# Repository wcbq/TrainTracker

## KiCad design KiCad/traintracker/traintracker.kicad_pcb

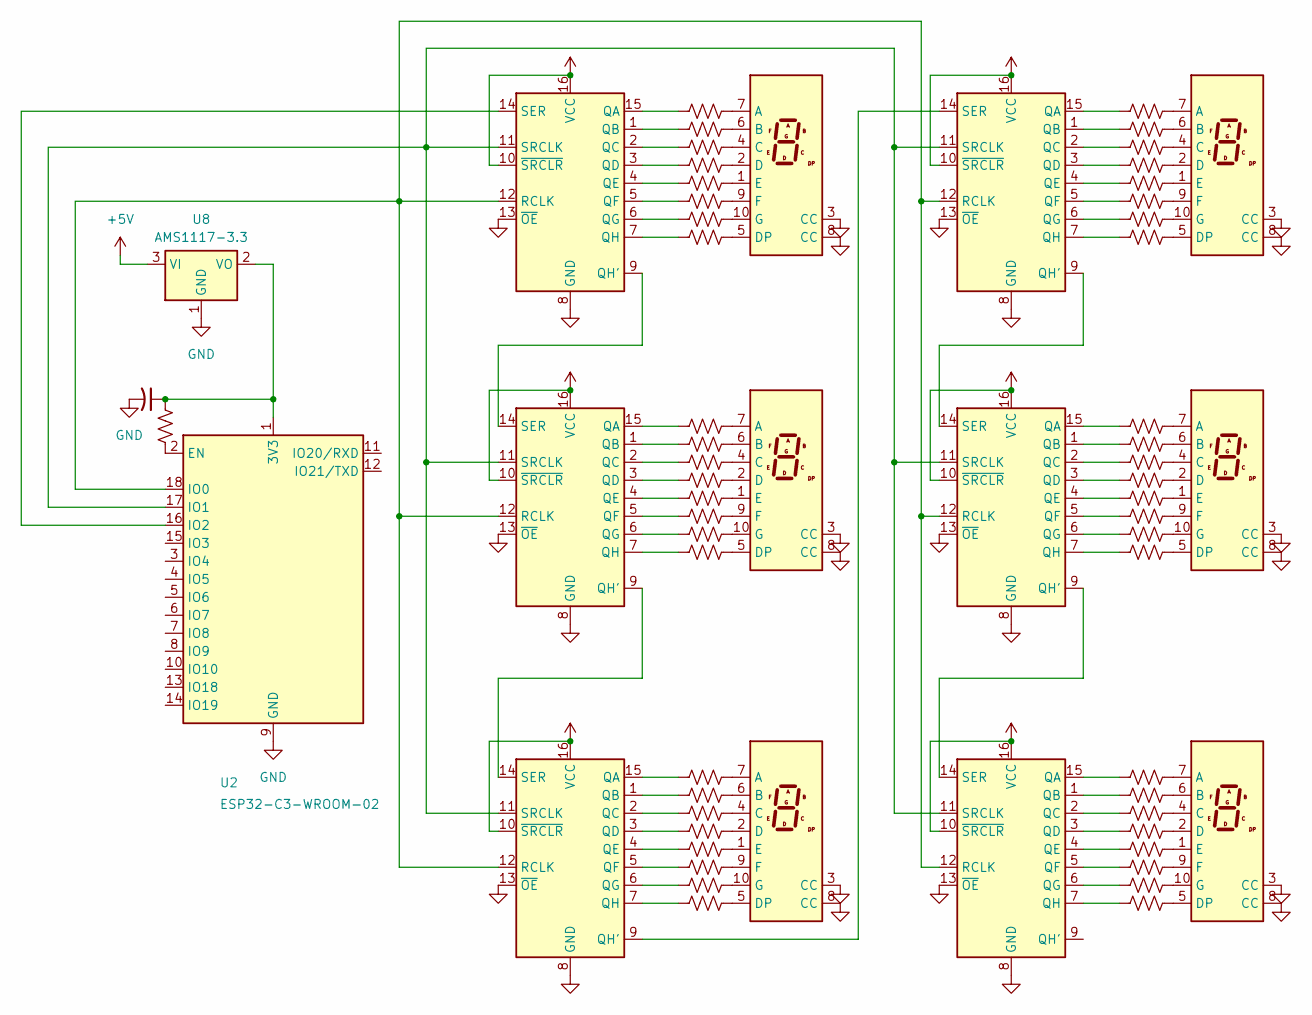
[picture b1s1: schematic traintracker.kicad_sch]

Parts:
C2: C_Small_US; CP_Elec_3x5.3
R1, R2, R3, R4, R5, R6, R7, R8, R9, R10, R11, R12, R13, R14, R15, R16, R17, R18, R19, R20, R21, R22, R23, R24, R25, R26, R27, R28, R29, R30, R31, R32, R33, R34, R35, R36, R37, R38, R39, R40, R41, R42, R43, R44, R45, R46, R47, R48, R50: R_US; R_0201_0603Metric
U1, U3, U4, U5, U6, U7: 74HC595; SOIC-16_3.9x9.9mm_P1.27mm
U2: ESP32-C3-WROOM-02
U8: AMS1117-3.3; SOT-223-3_TabPin2
U15, U16, U17, U18, U19, U20: D168K; D1X8K

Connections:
+5V: U1.10 (~SRCLR), U1.16 (VCC), U3.10 (~SRCLR), U3.16 (VCC), U4.10 (~SRCLR), U4.16 (VCC), U5.10 (~SRCLR), U5.16 (VCC), U6.10 (~SRCLR), U6.16 (VCC), U7.10 (~SRCLR), U7.16 (VCC), U8.3 (VI)
GND: C2.2, U1.8 (GND), U1.13 (~OE), U2.9 (GND), U2.19 (GND), U3.8 (GND), U3.13 (~OE), U4.8 (GND), U4.13 (~OE), U5.8 (GND), U5.13 (~OE), U6.8 (GND), U6.13 (~OE), U7.8 (GND), U7.13 (~OE), U8.1 (GND), U15.3 (CC), U15.8 (CC), U16.3 (CC), U16.8 (CC), U17.3 (CC), U17.8 (CC), U18.3 (CC), U18.8 (CC), U19.3 (CC), U19.8 (CC), U20.3 (CC), U20.8 (CC)
unnamed: R1.2, U1.15 (QA)
unnamed: R2.2, U1.1 (QB)
unnamed: R3.2, U1.2 (QC)
unnamed: R4.2, U1.3 (QD)
unnamed: R5.2, U1.4 (QE)
unnamed: R6.2, U1.5 (QF)
unnamed: R7.2, U1.6 (QG)
unnamed: U1.9 (QH'), U3.14 (SER)
unnamed: R8.2, U1.7 (QH)
unnamed: U1.12 (RCLK), U2.18 (IO0), U3.12 (RCLK), U4.12 (RCLK), U5.12 (RCLK), U6.12 (RCLK), U7.12 (RCLK)
unnamed: U1.14 (SER), U2.16 (IO2)
unnamed: U1.11 (SRCLK), U2.17 (IO1), U3.11 (SRCLK), U4.11 (SRCLK), U5.11 (SRCLK), U6.11 (SRCLK), U7.11 (SRCLK)
unnamed: C2.1, R50.1, U2.1 (3V3), U8.2 (VO)
unnamed: R50.2, U2.2 (EN)
unnamed: R9.2, U3.15 (QA)
unnamed: R10.2, U3.1 (QB)
unnamed: R11.2, U3.2 (QC)
unnamed: R12.2, U3.3 (QD)
unnamed: R13.2, U3.4 (QE)
unnamed: R14.2, U3.5 (QF)
unnamed: R15.2, U3.6 (QG)
unnamed: U3.9 (QH'), U4.14 (SER)
unnamed: R16.2, U3.7 (QH)
unnamed: R17.2, U4.15 (QA)
unnamed: R18.2, U4.1 (QB)
unnamed: R19.2, U4.2 (QC)
unnamed: R20.2, U4.3 (QD)
unnamed: R21.2, U4.4 (QE)
unnamed: R22.2, U4.5 (QF)
unnamed: R23.2, U4.6 (QG)
unnamed: U4.9 (QH'), U5.14 (SER)
unnamed: R24.2, U4.7 (QH)
unnamed: R25.2, U5.15 (QA)
unnamed: R26.2, U5.1 (QB)
unnamed: R27.2, U5.2 (QC)
unnamed: R28.2, U5.3 (QD)
unnamed: R29.2, U5.4 (QE)
unnamed: R30.2, U5.5 (QF)
unnamed: R31.2, U5.6 (QG)
unnamed: U5.9 (QH'), U6.14 (SER)
unnamed: R32.2, U5.7 (QH)
unnamed: R33.2, U6.15 (QA)
unnamed: R34.2, U6.1 (QB)
unnamed: R35.2, U6.2 (QC)
unnamed: R36.2, U6.3 (QD)
unnamed: R37.2, U6.4 (QE)
unnamed: R38.2, U6.5 (QF)
unnamed: R39.2, U6.6 (QG)
unnamed: U6.9 (QH'), U7.14 (SER)
unnamed: R40.2, U6.7 (QH)
unnamed: R41.2, U7.15 (QA)
unnamed: R42.2, U7.1 (QB)
unnamed: R43.2, U7.2 (QC)
unnamed: R44.2, U7.3 (QD)
unnamed: R45.2, U7.4 (QE)
unnamed: R46.2, U7.5 (QF)
unnamed: R47.2, U7.6 (QG)
unnamed: R48.2, U7.7 (QH)
unnamed: R1.1, U15.7 (A)
unnamed: R2.1, U15.6 (B)
unnamed: R3.1, U15.4 (C)
unnamed: R4.1, U15.2 (D)
unnamed: R8.1, U15.5 (DP)
unnamed: R5.1, U15.1 (E)
unnamed: R6.1, U15.9 (F)
unnamed: R7.1, U15.10 (G)
unnamed: R9.1, U16.7 (A)
unnamed: R10.1, U16.6 (B)
unnamed: R11.1, U16.4 (C)
unnamed: R12.1, U16.2 (D)
unnamed: R16.1, U16.5 (DP)
unnamed: R13.1, U16.1 (E)
unnamed: R14.1, U16.9 (F)
unnamed: R15.1, U16.10 (G)
unnamed: R25.1, U17.7 (A)
unnamed: R26.1, U17.6 (B)
unnamed: R27.1, U17.4 (C)
unnamed: R28.1, U17.2 (D)
unnamed: R32.1, U17.5 (DP)
unnamed: R29.1, U17.1 (E)
unnamed: R30.1, U17.9 (F)
unnamed: R31.1, U17.10 (G)
unnamed: R17.1, U18.7 (A)
unnamed: R18.1, U18.6 (B)
unnamed: R19.1, U18.4 (C)
unnamed: R20.1, U18.2 (D)
unnamed: R24.1, U18.5 (DP)
unnamed: R21.1, U18.1 (E)
unnamed: R22.1, U18.9 (F)
unnamed: R23.1, U18.10 (G)
unnamed: R33.1, U19.7 (A)
unnamed: R34.1, U19.6 (B)
unnamed: R35.1, U19.4 (C)
unnamed: R36.1, U19.2 (D)
unnamed: R40.1, U19.5 (DP)
unnamed: R37.1, U19.1 (E)
unnamed: R38.1, U19.9 (F)
unnamed: R39.1, U19.10 (G)
unnamed: R41.1, U20.7 (A)
unnamed: R42.1, U20.6 (B)
unnamed: R43.1, U20.4 (C)
unnamed: R44.1, U20.2 (D)
unnamed: R48.1, U20.5 (DP)
unnamed: R45.1, U20.1 (E)
unnamed: R46.1, U20.9 (F)
unnamed: R47.1, U20.10 (G)

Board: 2 copper layers, 64 parts (0 on the bottom side), 108 nets, no tracks yet.

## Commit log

2026-05-04 Add datasheets
    add datasheets for 7 segment display(3191AS) and shift register (SNx4HC595)
2026-05-04 Upload KiCad
    Add current KiCad files
2026-05-04 Add apitest.py
    test file for getting data from mta's various apis, and scheduling ferry times.
2026-05-04 Rename apitest.py to apitest_si.py
2026-05-16 wifitest.py
    connects to wifi and calls mta api on esp32 using micropython
